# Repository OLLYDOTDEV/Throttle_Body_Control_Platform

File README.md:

# Throttle Body Control Platform (TBCP)

## Project Overview
The **Electronic Throttle Body Control Platform (TBCP)** is a custom real-time controller designed to test advanced control methods for electronic throttle bodies in automotive applications. This project aims to overcome the limitations of existing hardware solutions at Wintec and provide a reliable platform for experimenting with cutting-edge technologies such as adaptive tracking control.

## Key Objectives
- Create a reliable hardware platform for testing various control methods
- Improve the response time of the electronic throttle body
- Minimize signal error from the feedback sensor
- Develop and simplify a comprehensive wiring diagram
- Implement a control platform to enhance throttle body valve responsiveness and accuracy

## Features

### Hardware
- Custom PCB design
- H-bridge IC for motor control
- Voltage regulator for stable power supply
- Microcontroller selection for real-time control
- User interface with LED indicators and buttons
- Reversed voltage protection

### Software
- Simulink Real-Time Control for rapid testing and tuning
- Signal calibration mode for improved system adaptability
- Signal conditioning for input/output management
- Multiple control modes (Proportional, PID, and ADRC Control)
- Error detection function for monitoring voltage levels

## Project Methodology
- Analyze existing throttle control methods and technologies
- Apply Scrum framework for project management
- Implement control algorithms on common microcontroller platforms
- Develop custom real-time controllers for advanced control methodologies
- Employ data logging equipment for performance metrics
- Conduct comparative analysis between simulation and practical testing
- Ensure consistency in testing methods and equipment calibration

## Data Collection
- Relevant electrical parameters
- Valve response time and signal propagation
- Pedal input, valve feedback, and controller I/O values

## Installation and Setup
See final report Appendix 

## Authors
- Oliver Bell
- Piyapat Srisawat

### Academic Supervisor
- Mohammad AI-Rawi

## License
This project is licensed under the MIT License.

## Acknowledgments
- Wintec (Waikato Institute of Technology) for supporting this project

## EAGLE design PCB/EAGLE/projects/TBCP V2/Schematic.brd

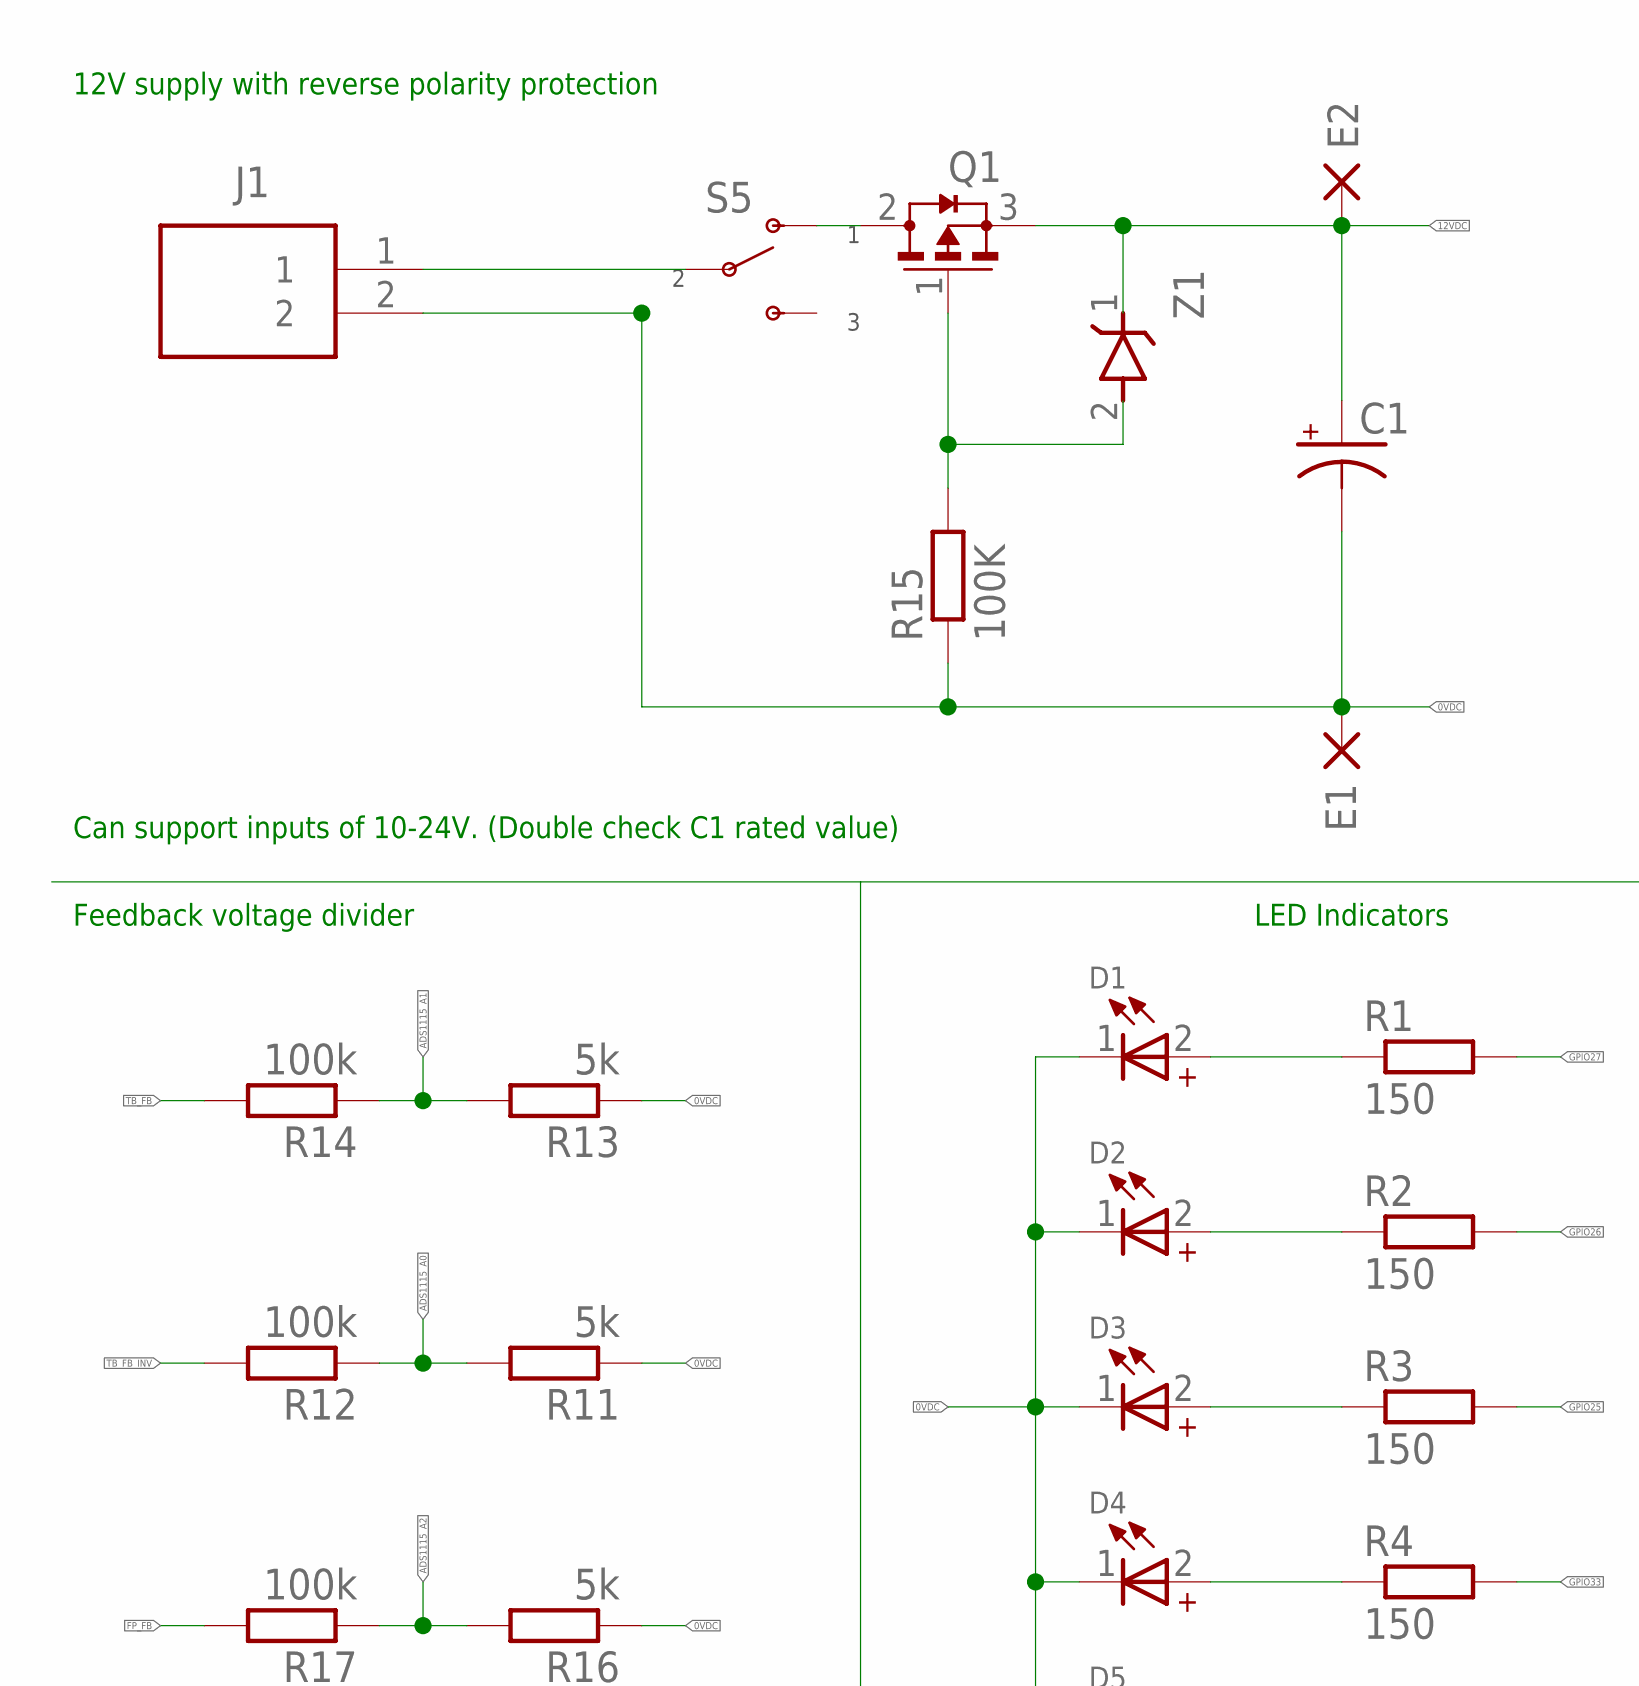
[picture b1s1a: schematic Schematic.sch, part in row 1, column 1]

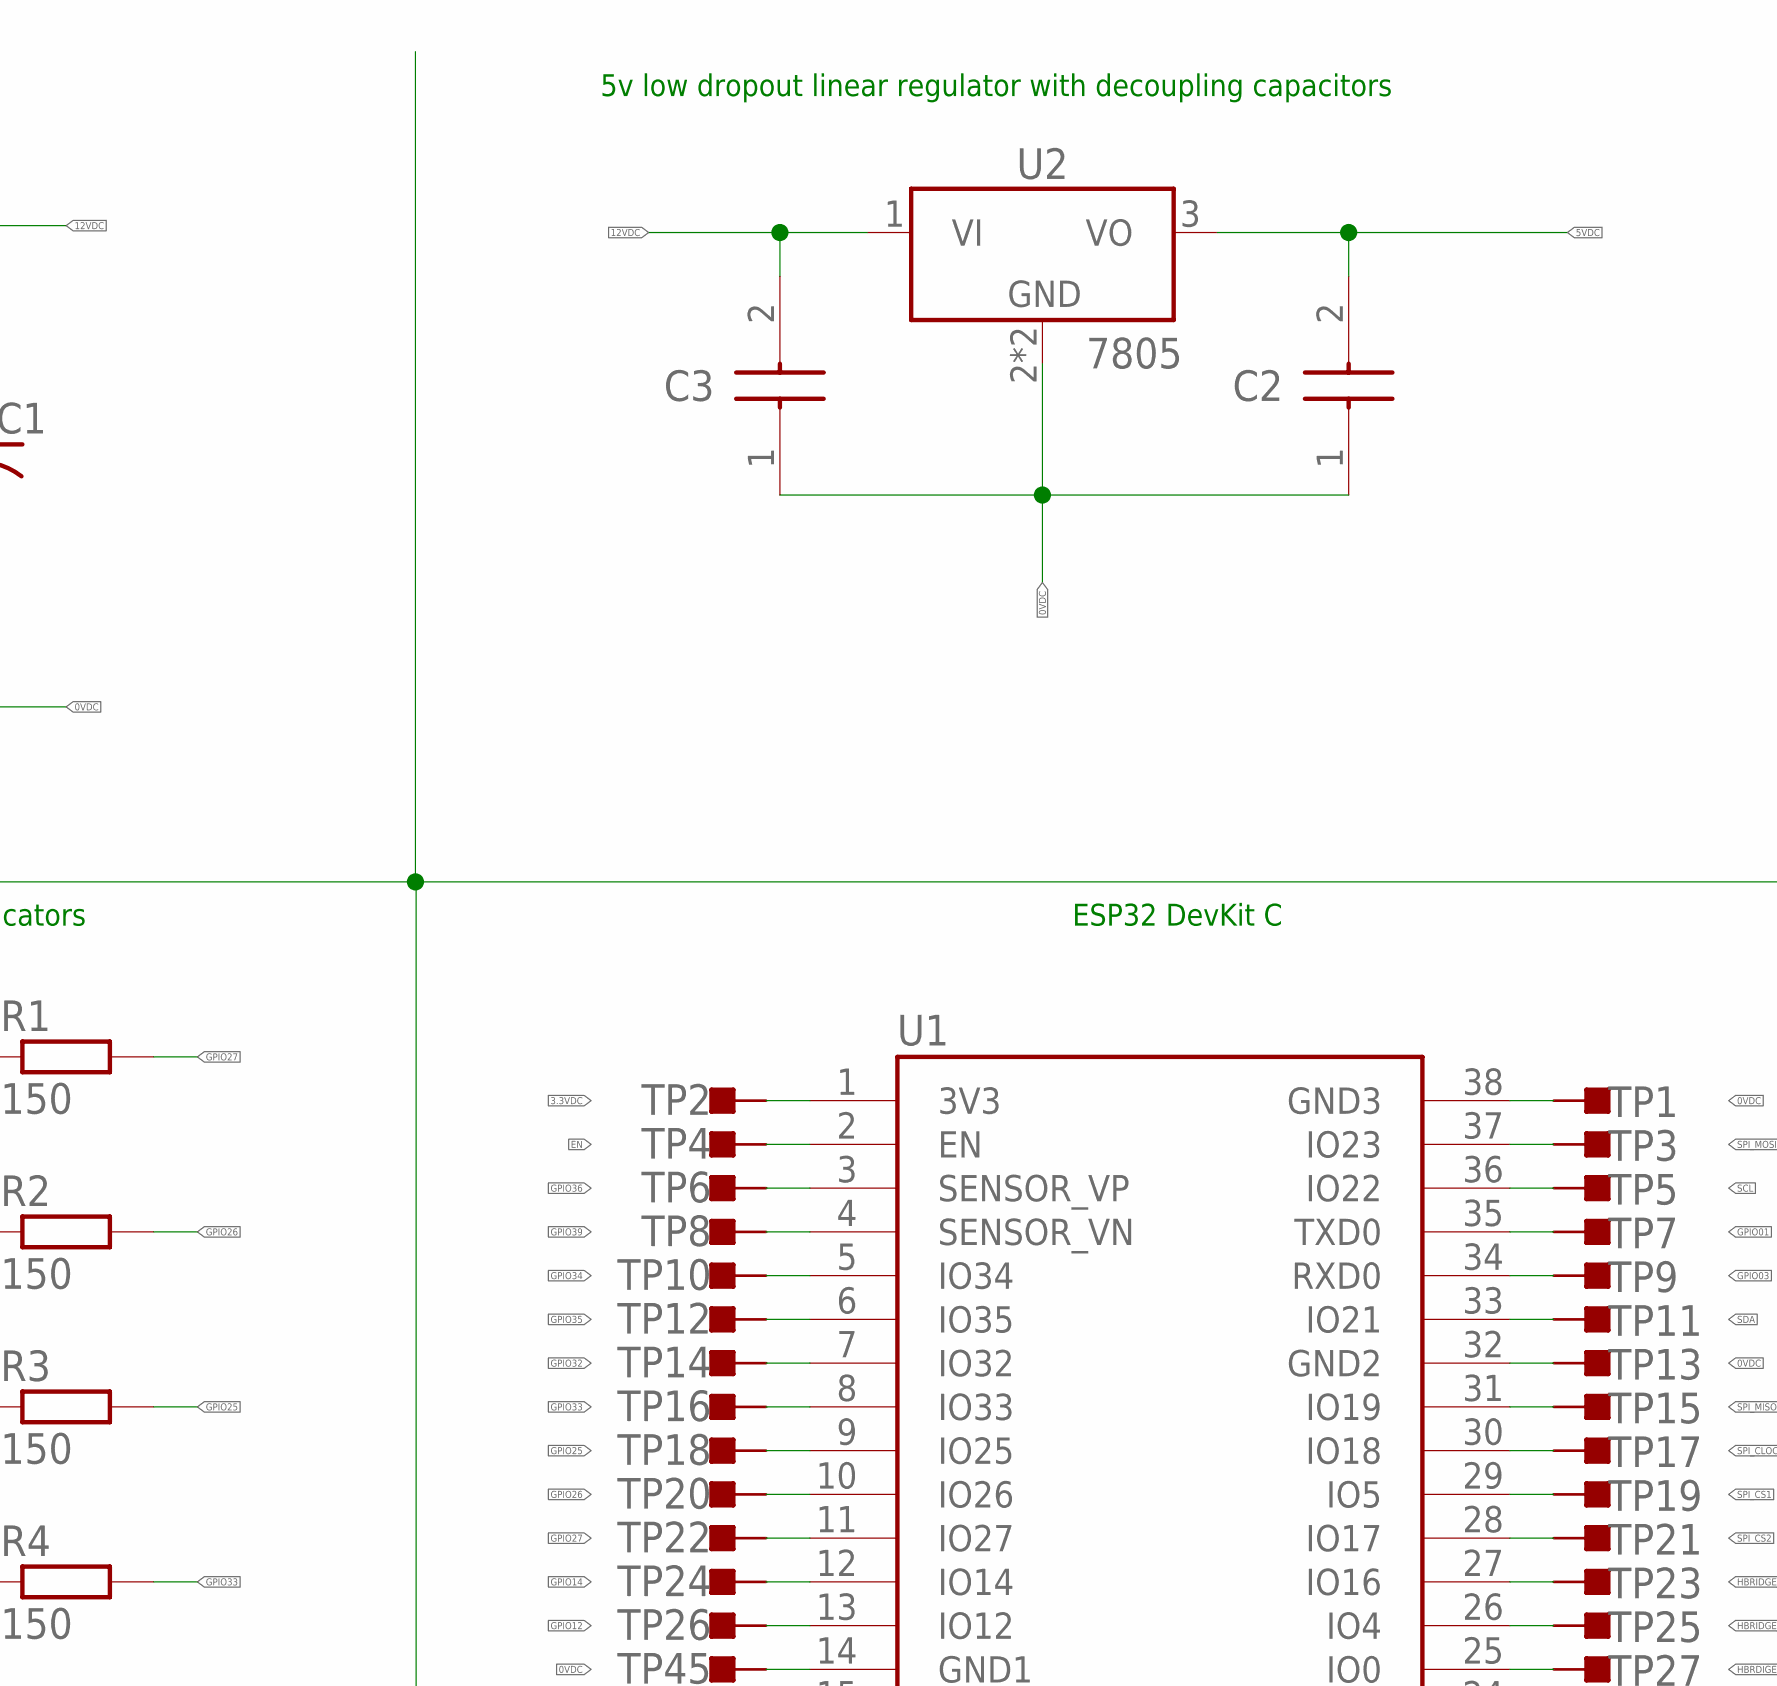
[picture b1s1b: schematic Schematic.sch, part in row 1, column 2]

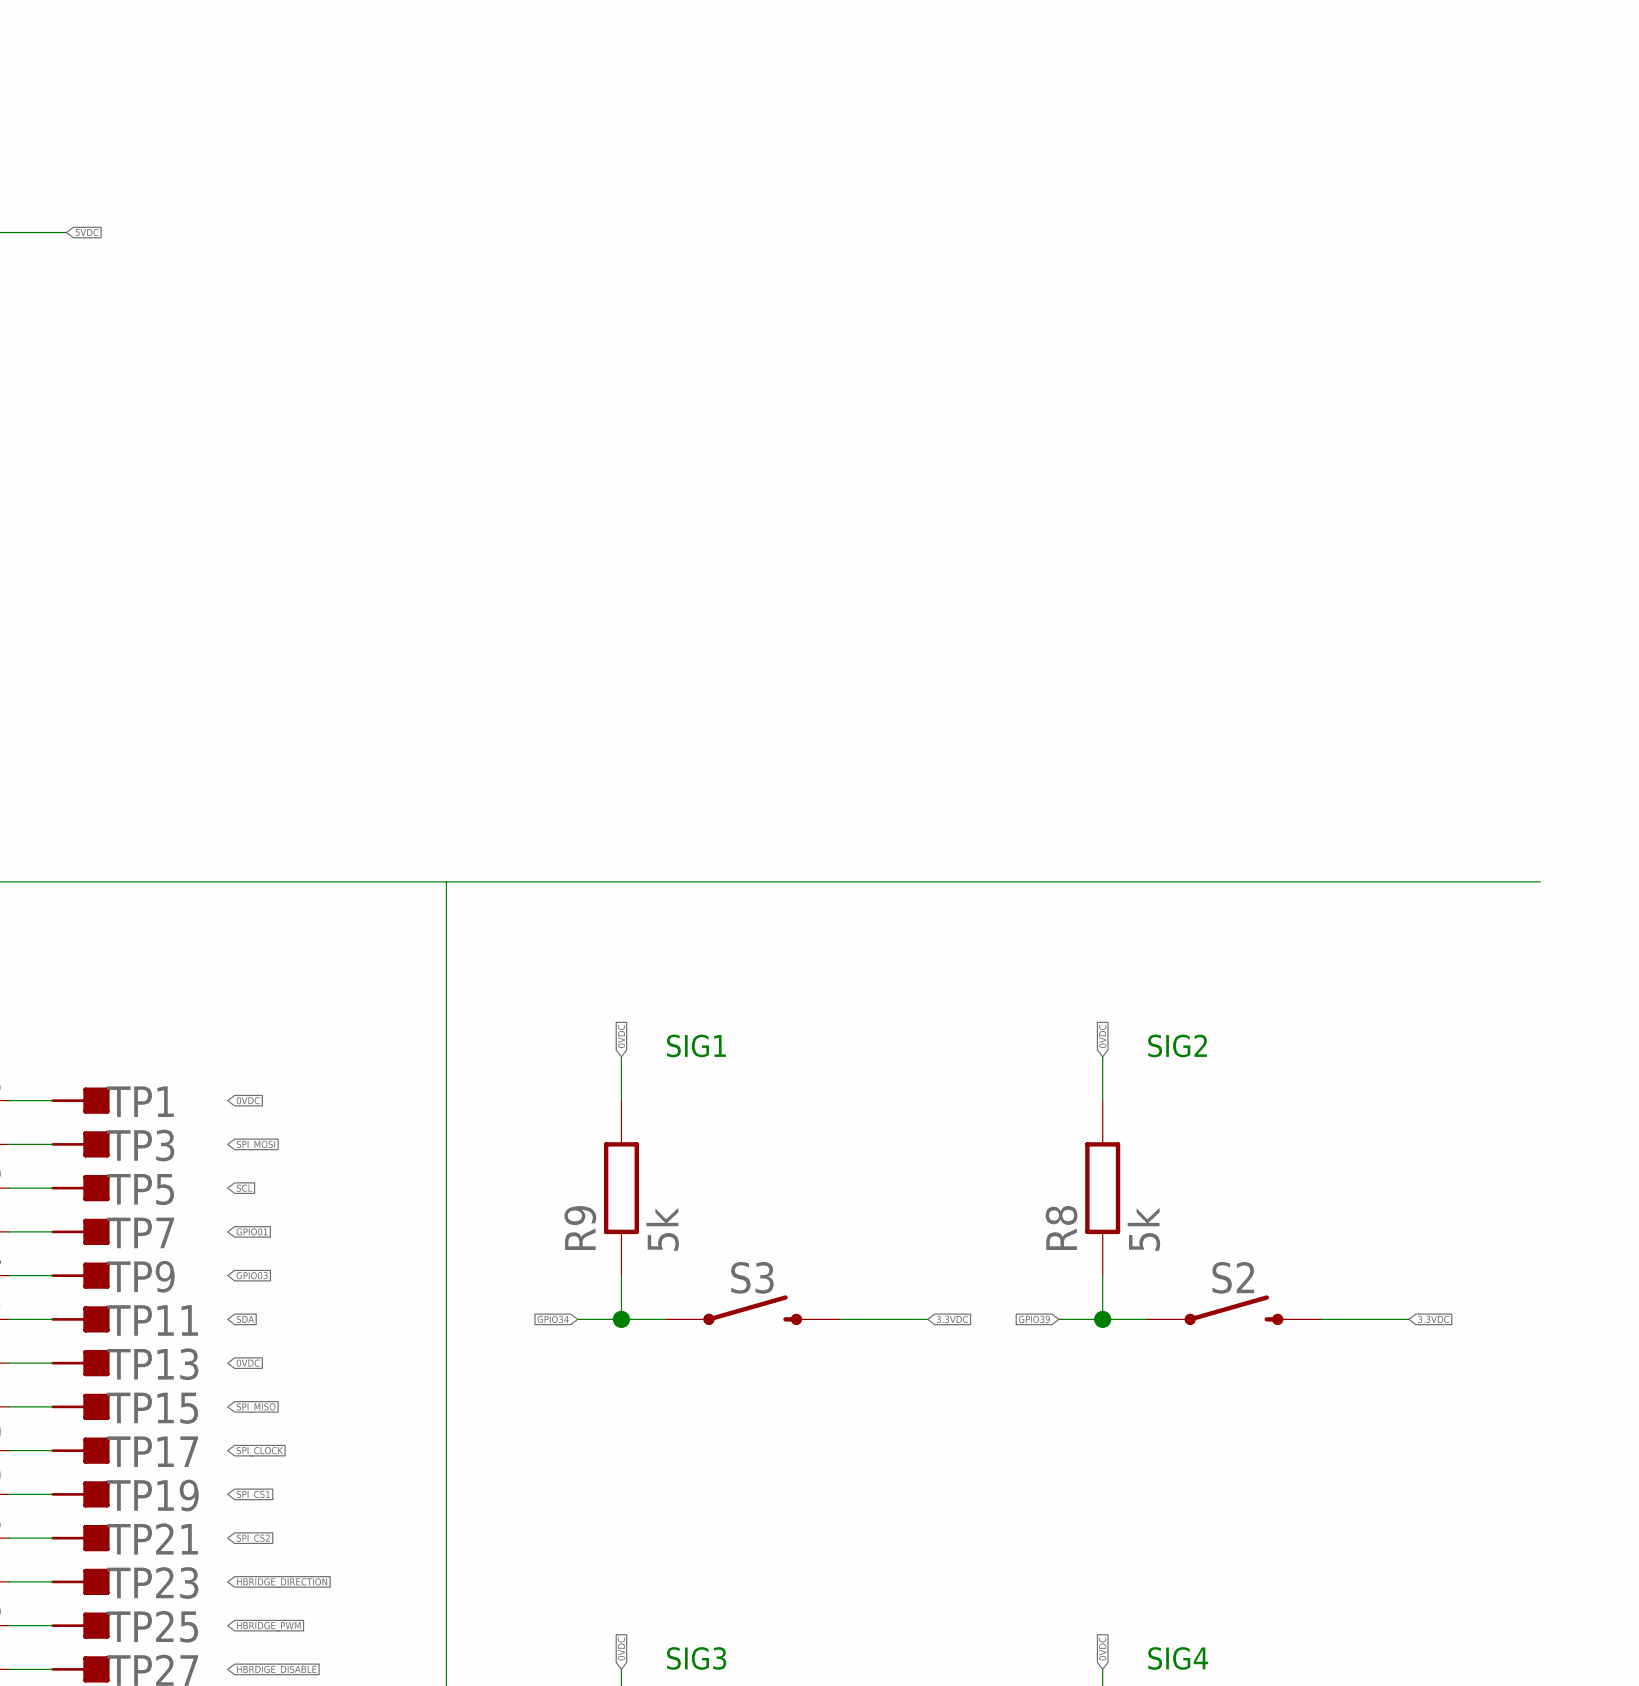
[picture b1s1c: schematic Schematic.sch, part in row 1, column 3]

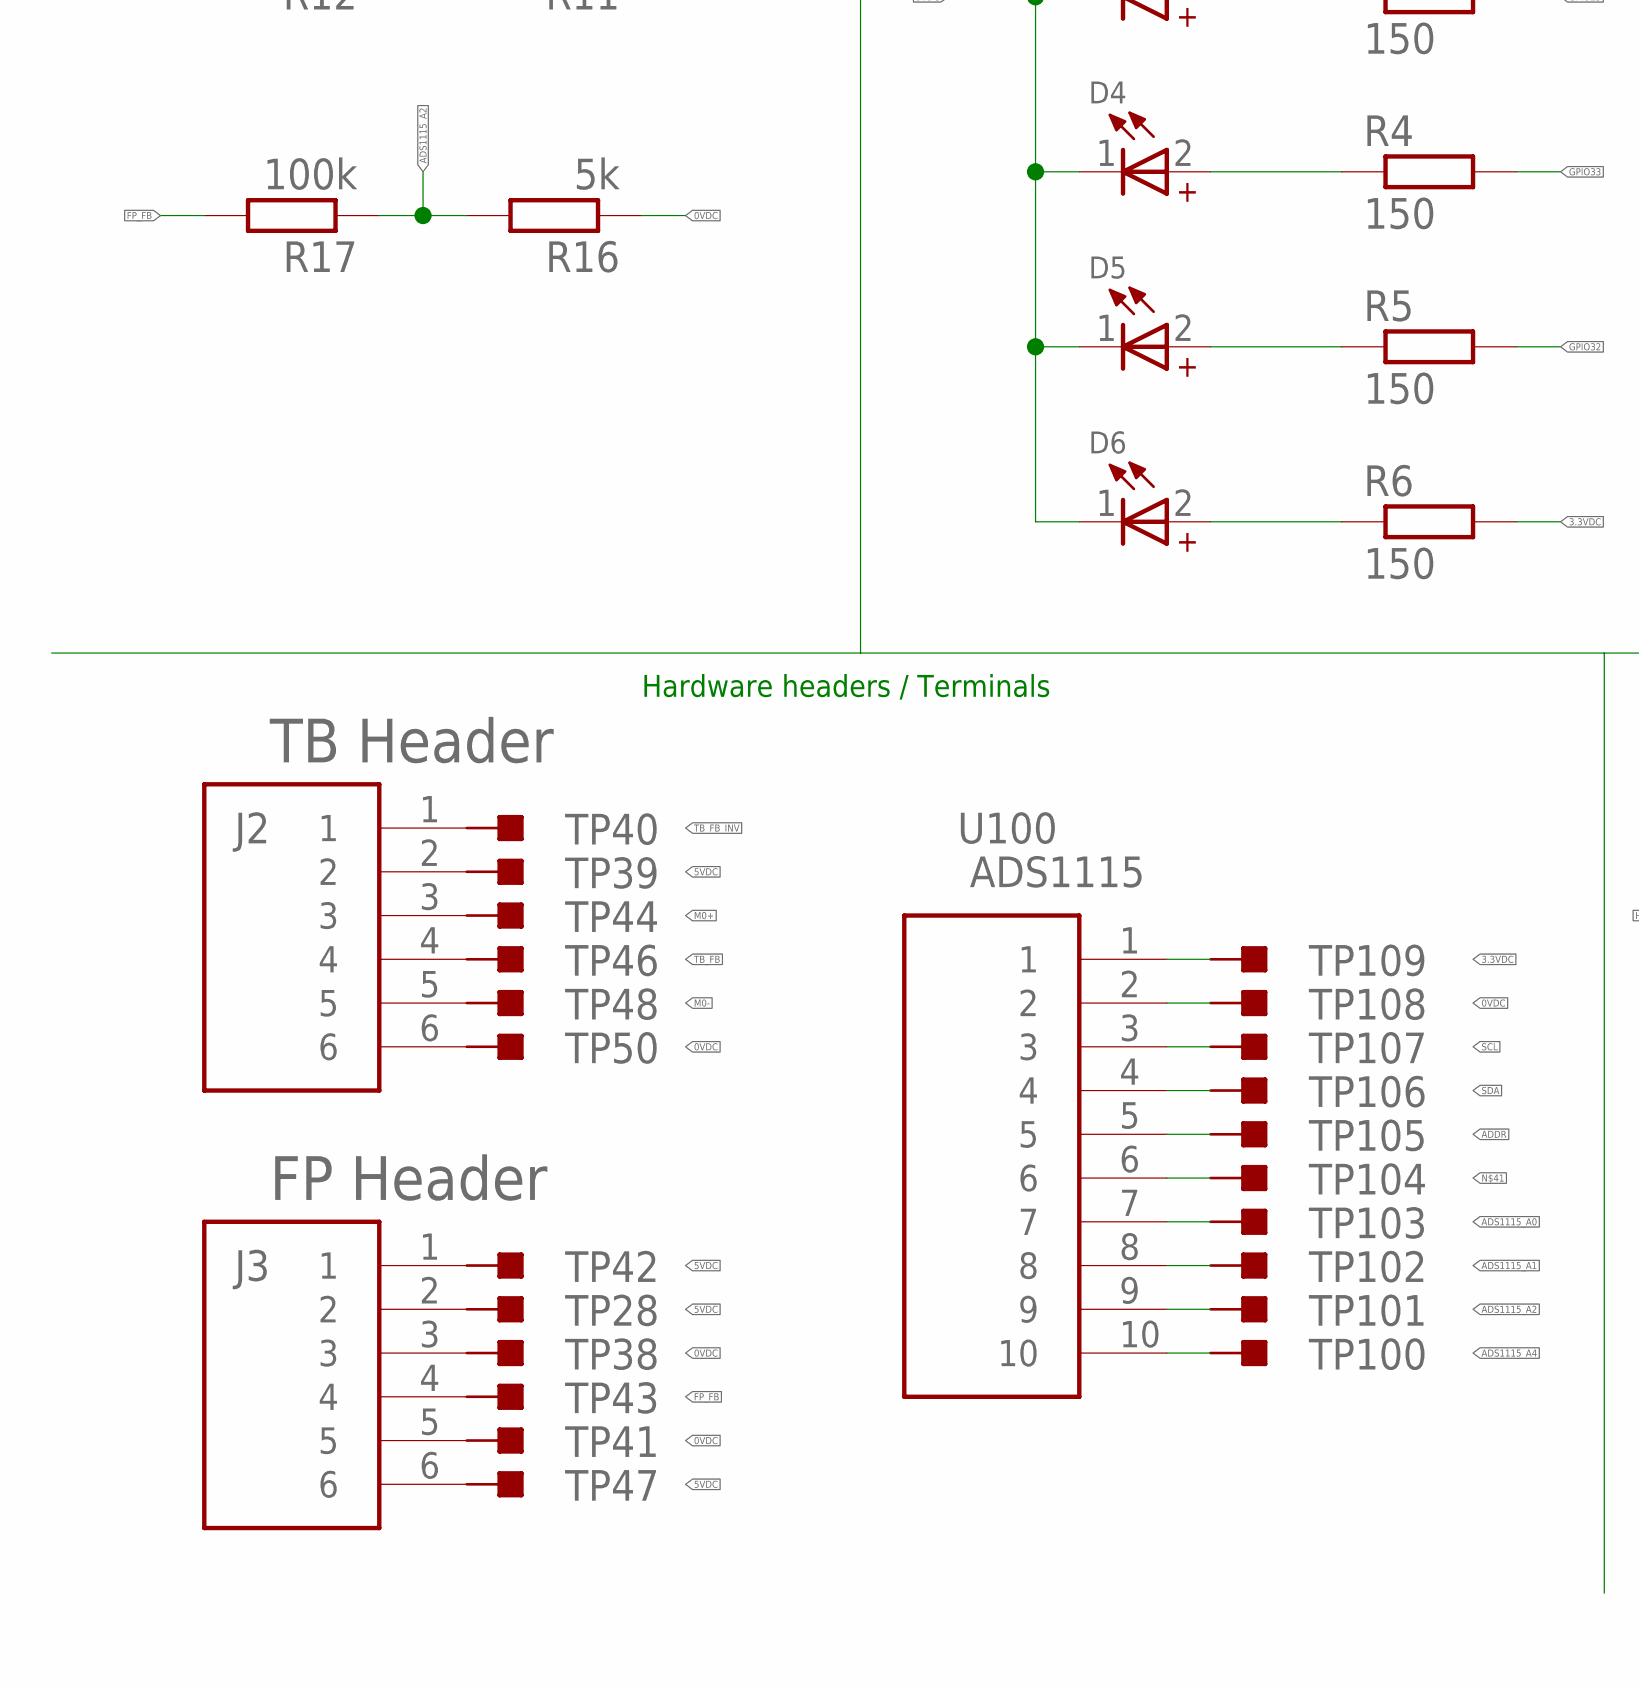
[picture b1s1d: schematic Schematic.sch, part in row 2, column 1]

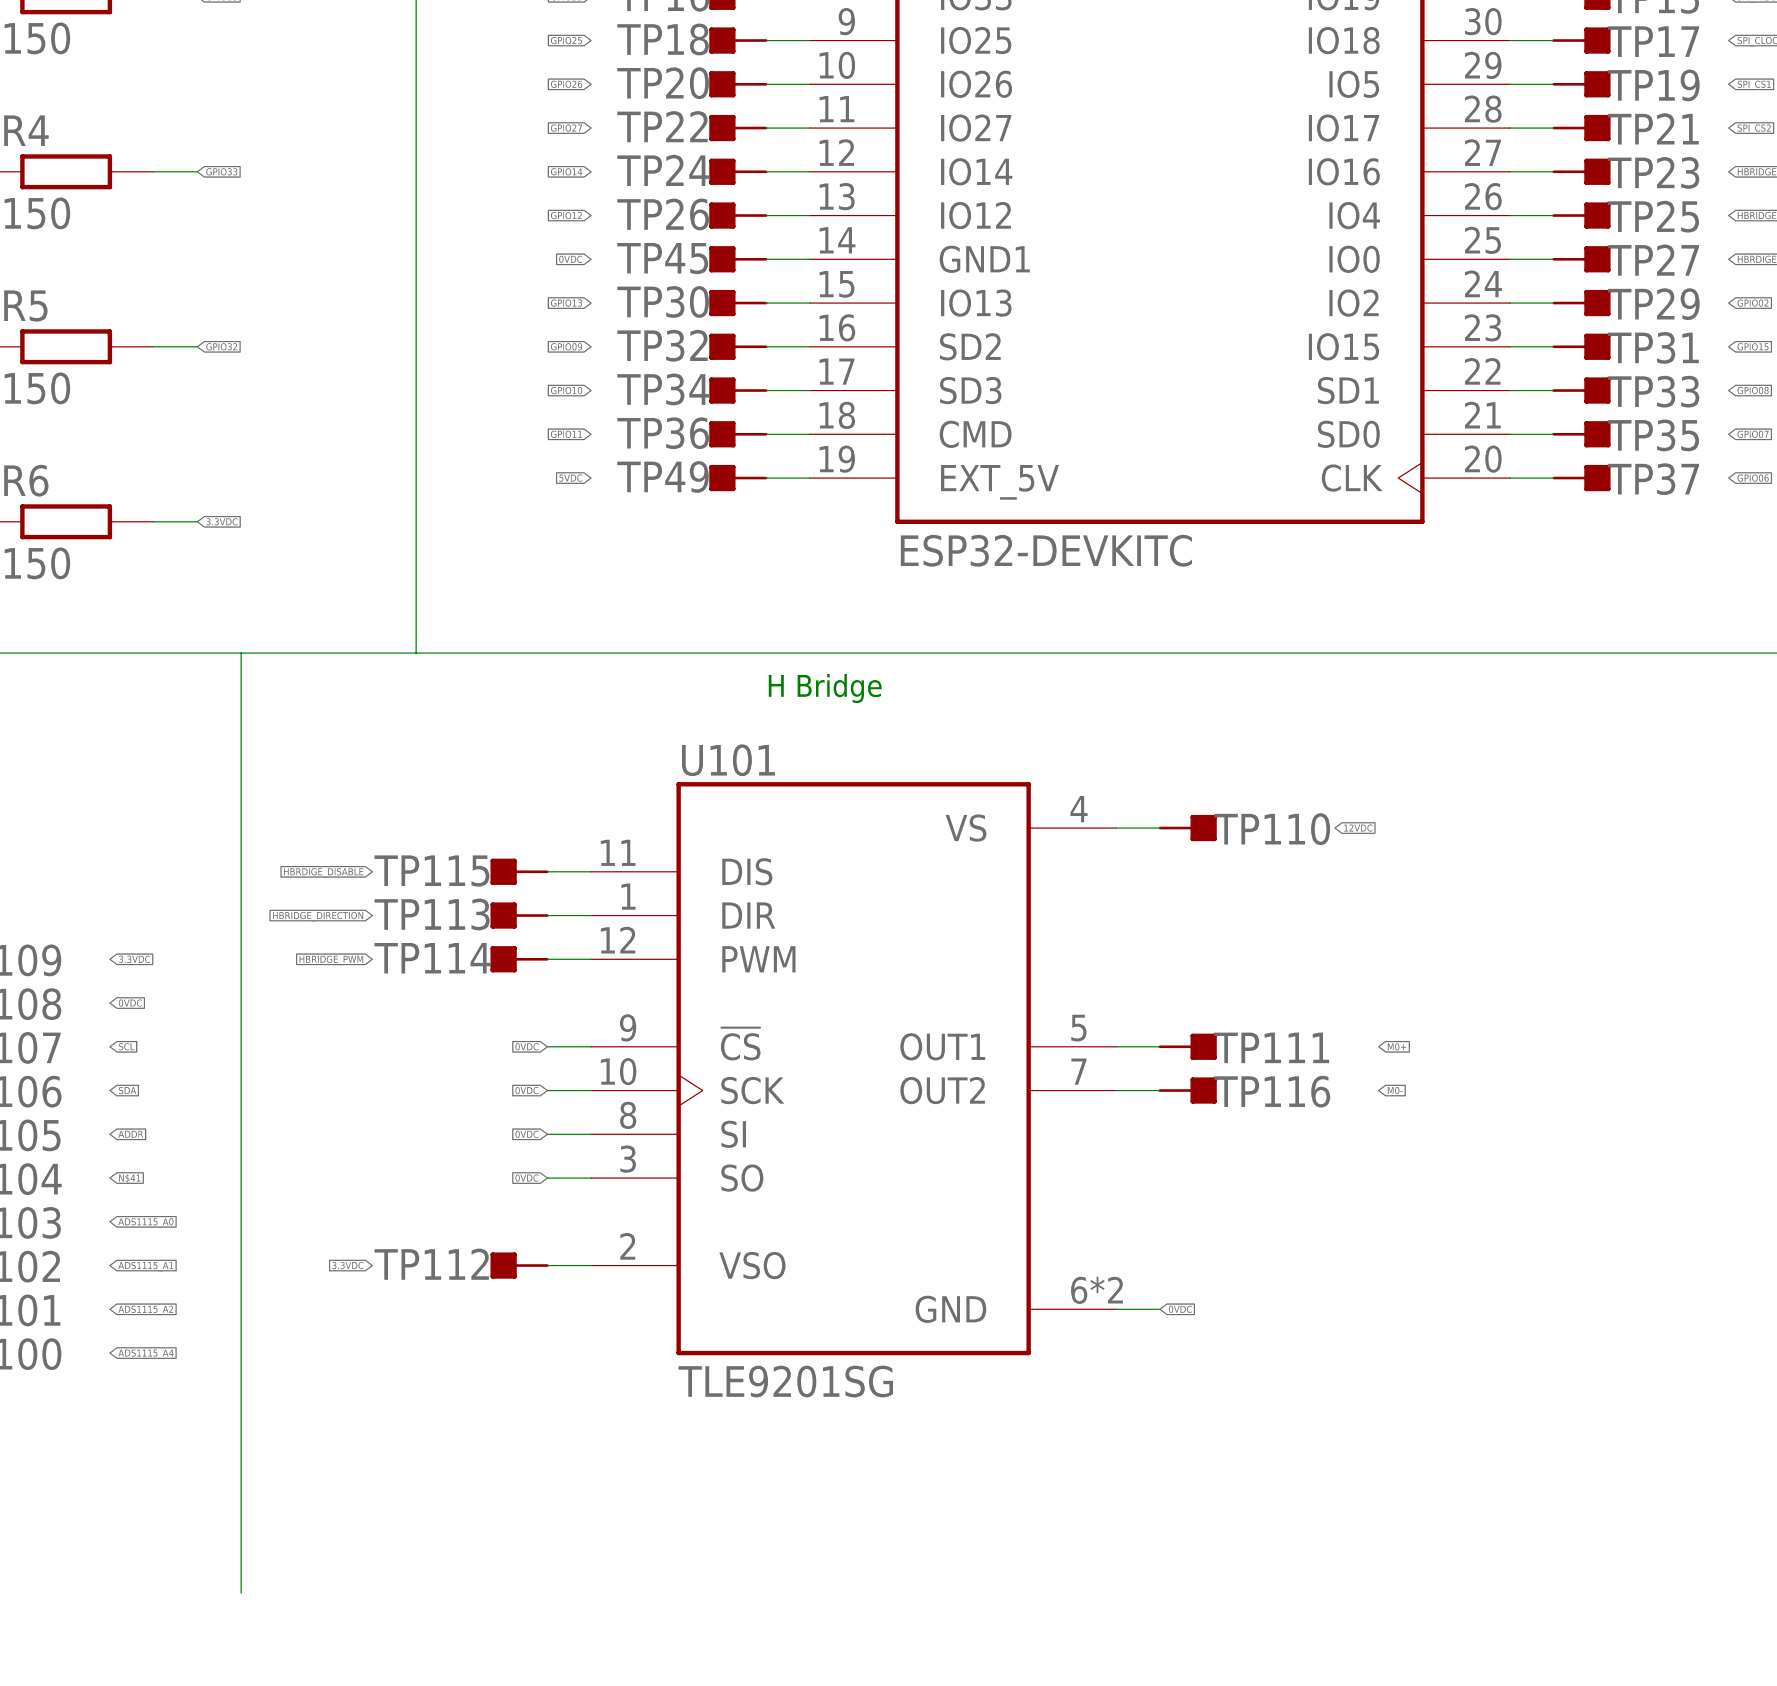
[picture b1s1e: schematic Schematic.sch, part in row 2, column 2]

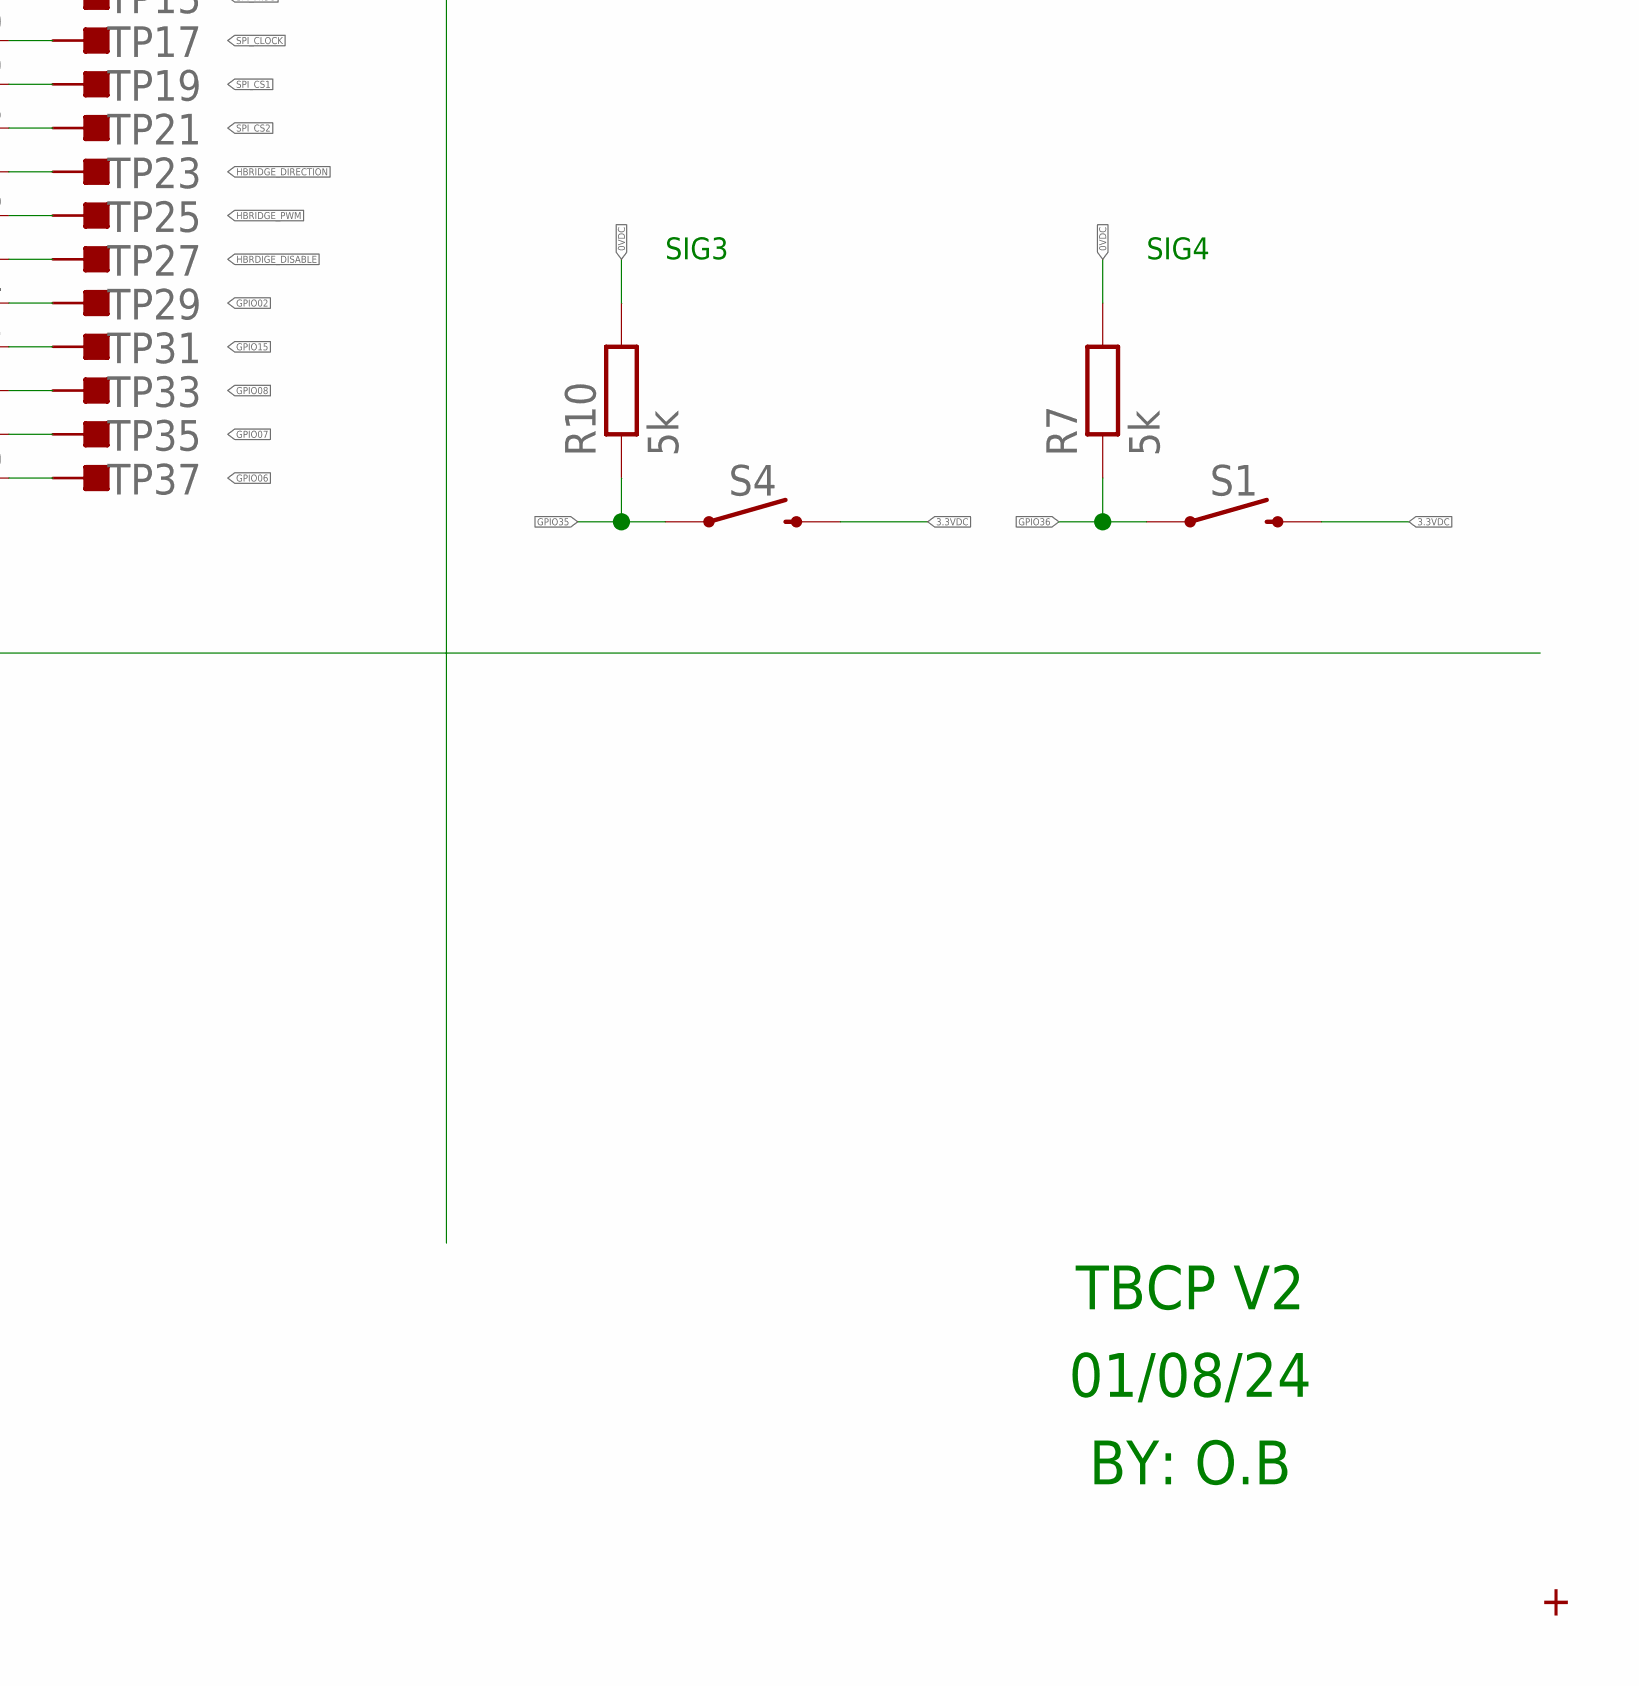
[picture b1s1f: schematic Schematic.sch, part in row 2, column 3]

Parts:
C1: CAPACITOR-PTAP5-80; TAP5-80
C2, C3: C0805C224J1RACTU; C0805
D1, D2, D3, D4, D5, D6: 150080AS75000; WL-SMCW_0805
E1, E2: DPADS_PAD-0400-S; DPADS_0400-S
J1: 12 Supply; 1757284
J2: TB Header; 1757284
J3: FP Header; 1757284
Q1: DMP4025LK3Q-13; DMP4025LK3Q13
R1, R2, R3, R4, R5, R6: 150; R2012
R7, R8, R9, R10, R11, R13, R16: 5k; R2012
R12, R14, R17: 100k; R2012
R15: 100K; R2012
S1, S2, S3, S4: MOMENTARY-SWITCH-SPST; TACTILE_SWITCH_PTH_6.0MM
S5: 500SSP1S1M6QEA
TP1, TP3, TP5, TP7, TP9, TP11, TP13, TP15, TP16, TP17, TP18, TP19, TP20, TP21, TP22, TP23, TP24, TP25, TP26, TP27, TP28, TP29, TP30, TP31, TP32, TP33, TP34, TP35, TP36, TP37, TP38, TP39, TP40, TP41, TP42, TP43, TP44, TP45, TP46, TP47, TP48, TP49, TP50, TP100, TP101, TP102, TP103, TP104, TP105, TP106, TP107, TP108, TP109, TP110, TP111, TP112, TP113, TP114, TP115, TP116: TESTPOINT_TPS-SMD-10SN; TESTPOINT_SMD-10SN
TP2: 3V3; TESTPOINT_SMD-10SN
TP4: EN; TESTPOINT_SMD-10SN
TP6: GPIO36; TESTPOINT_SMD-10SN
TP8: GPIO39; TESTPOINT_SMD-10SN
TP10: GPIO34; TESTPOINT_SMD-10SN
TP12: GPIO35; TESTPOINT_SMD-10SN
TP14: GPIO32; TESTPOINT_SMD-10SN
U1: ESP32-DEVKITC; MODULE_ESP32-DEVKITC
U2: 7805; SOT230P700X170-4
U100: ADS1115; ADS111X
U101: TLE9201SG; IC_TLE9201SG
U$1: WINTEC
Z1: MM5Z10VT1G; SODFL1608X70N

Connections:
0VDC: C1.-, C2.1, C3.1, D1.1 (-), D2.1 (-), D3.1 (-), D4.1 (-), D5.1 (-), D6.1 (-), E1.PAD, J1.2, J2.6, J3.3, J3.5, R7.2, R8.2, R9.2, R10.2, R11.1, R13.1, R15.1, R16.1, TP1.TP, TP13.TP, TP28.TP, TP41.TP, TP45.TP, TP50.TP, TP108.TP, U1.14 (GND1), U1.32 (GND2), U1.38 (GND3), U2.2 (GND), U2.4 (GND), U100.2, U101.3 (SO), U101.6 (GND), U101.8 (SI), U101.9 (!CS), U101.10 (SCK), U101.13 (GND)
3.3VDC: R6.2, S1.3 (2), S2.3 (2), S3.3 (2), S4.3 (2), TP2.TP, TP109.TP, TP112.TP, U1.1 (3V3), U100.1, U101.2 (VSO)
5VDC: C2.2, J2.2, J3.1, J3.2, J3.6, TP38.TP, TP39.TP, TP42.TP, TP47.TP, TP49.TP, U1.19 (EXT_5V), U2.3 (VO)
12VDC: C1.+, C3.2, E2.PAD, Q1.3 (S), TP110.TP, U2.1 (VI), U101.4 (VS), Z1.1 (K)
ADDR: TP105.TP, U100.5
ADS1115_A0: R11.2, R12.1, TP103.TP, U100.7
ADS1115_A1: R13.2, R14.1, TP102.TP, U100.8
ADS1115_A2: R16.2, R17.1, TP101.TP, U100.9
ADS1115_A4: TP100.TP, U100.10
EN: TP4.TP, U1.2 (EN)
FP_FB: J3.4, R17.2, TP43.TP
GPIO01: TP7.TP, U1.35 (TXD0)
GPIO02: TP29.TP, U1.24 (IO2)
GPIO03: TP9.TP, U1.34 (RXD0)
GPIO06: TP37.TP, U1.20 (CLK)
GPIO07: TP35.TP, U1.21 (SD0)
GPIO08: TP33.TP, U1.22 (SD1)
GPIO09: TP32.TP, U1.16 (SD2)
GPIO10: TP34.TP, U1.17 (SD3)
GPIO11: TP36.TP, U1.18 (CMD)
GPIO12: TP26.TP, U1.13 (IO12)
GPIO13: TP30.TP, U1.15 (IO13)
GPIO14: TP24.TP, U1.12 (IO14)
GPIO15: TP31.TP, U1.23 (IO15)
GPIO25: R3.2, TP18.TP, U1.9 (IO25)
GPIO26: R2.2, TP20.TP, U1.10 (IO26)
GPIO27: R1.2, TP22.TP, U1.11 (IO27)
GPIO32: R5.2, TP14.TP, U1.7 (IO32)
GPIO33: R4.2, TP16.TP, U1.8 (IO33)
GPIO34: R9.1, S3.1, TP10.TP, U1.5 (IO34)
GPIO35: R10.1, S4.1, TP12.TP, U1.6 (IO35)
GPIO36: R7.1, S1.1, TP6.TP, U1.3 (SENSOR_VP)
GPIO39: R8.1, S2.1, TP8.TP, U1.4 (SENSOR_VN)
HBRDIGE_DISABLE: TP27.TP, TP115.TP, U1.25 (IO0), U101.11 (DIS)
HBRIDGE_DIRECTION: TP23.TP, TP113.TP, U1.27 (IO16), U101.1 (DIR)
HBRIDGE_PWM: TP25.TP, TP114.TP, U1.26 (IO4), U101.12 (PWM)
M0+: J2.3, TP44.TP, TP111.TP, U101.5 (OUT1)
M0-: J2.5, TP48.TP, TP116.TP, U101.7 (OUT2)
unnamed: J1.1, S5.2
unnamed: D6.2 (+), R6.1
unnamed: D1.2 (+), R1.1
unnamed: Q1.1 (G), R15.2, Z1.2 (A)
unnamed: D2.2 (+), R2.1
unnamed: D3.2 (+), R3.1
unnamed: D4.2 (+), R4.1
unnamed: D5.2 (+), R5.1
unnamed: Q1.2 (D), S5.1
unnamed: TP104.TP, U100.6
SCL: TP5.TP, TP107.TP, U1.36 (IO22), U100.3
SDA: TP11.TP, TP106.TP, U1.33 (IO21), U100.4
SPI_CLOCK: TP17.TP, U1.30 (IO18)
SPI_CS1: TP19.TP, U1.29 (IO5)
SPI_CS2: TP21.TP, U1.28 (IO17)
SPI_MISO: TP15.TP, U1.31 (IO19)
SPI_MOSI: TP3.TP, U1.37 (IO23)
TB_FB: J2.4, R14.2, TP46.TP
TB_FB_INV: J2.1, R12.2, TP40.TP

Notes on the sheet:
12V supply with reverse polarity protection
SIG3
SIG4
SIG1
SIG2
5v low dropout linear regulator with decoupling capacitors
Feedback voltage divider
Hardware headers / Terminals
H Bridge
LED Indicators
ESP32 DevKit C
TBCP V2
01/08/24
BY: O.B
Can support inputs of 10-24V. (Double check C1 rated value)

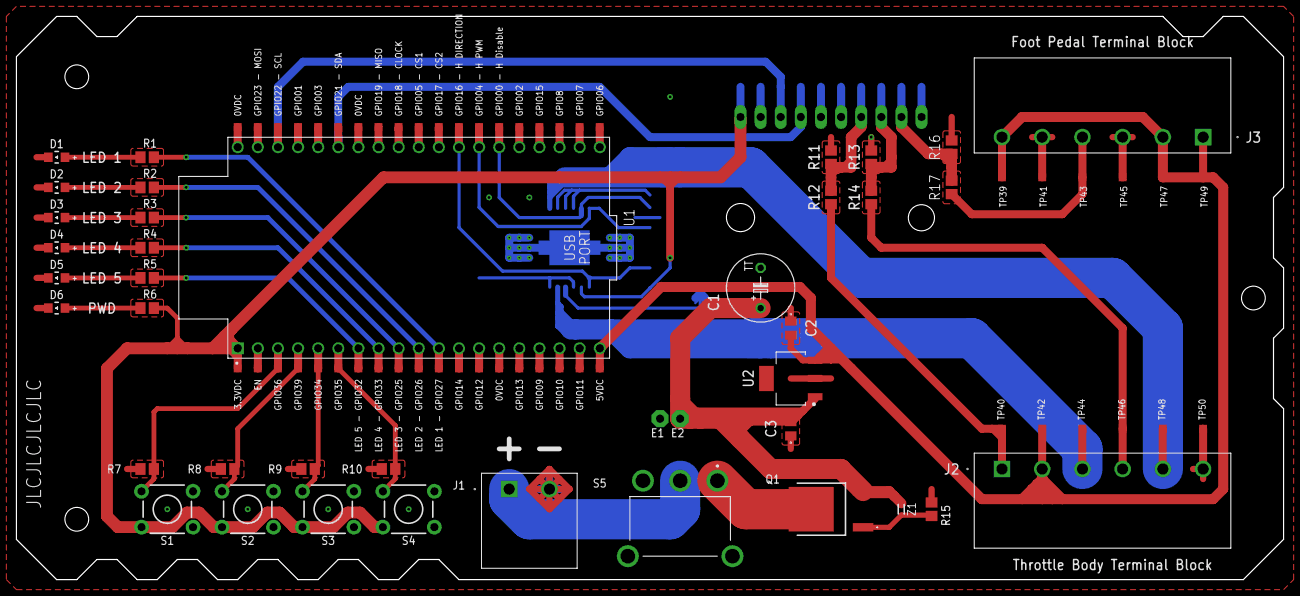
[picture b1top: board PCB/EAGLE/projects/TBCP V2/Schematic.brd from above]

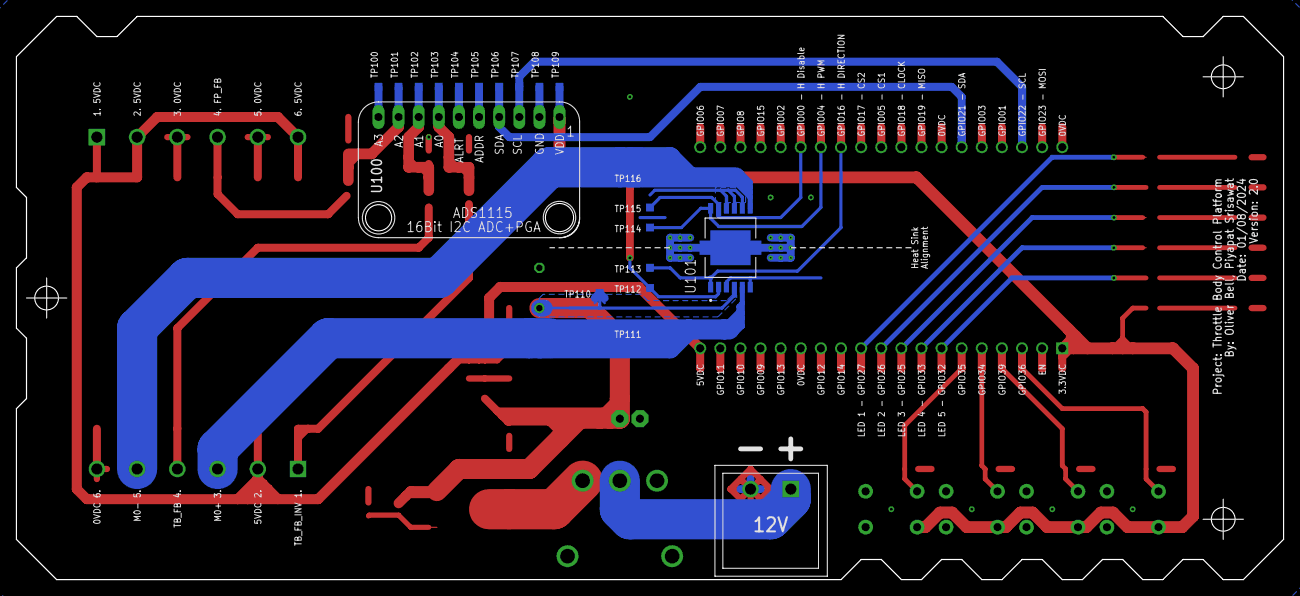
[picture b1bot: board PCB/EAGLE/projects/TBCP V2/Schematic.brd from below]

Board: 2 copper layers, 160.0 x 71.1 mm, 110 parts (19 on the bottom side), 57 nets.

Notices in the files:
parts and their libraries:
Wurth_LEDs_WL-SMCW: Copyright: Würth Elektronik
12mm TAC SWITCH: Licensing: Creative Commons ShareAlike 4.0 International - https://creativecommons.org/licenses/by-sa/4.0
